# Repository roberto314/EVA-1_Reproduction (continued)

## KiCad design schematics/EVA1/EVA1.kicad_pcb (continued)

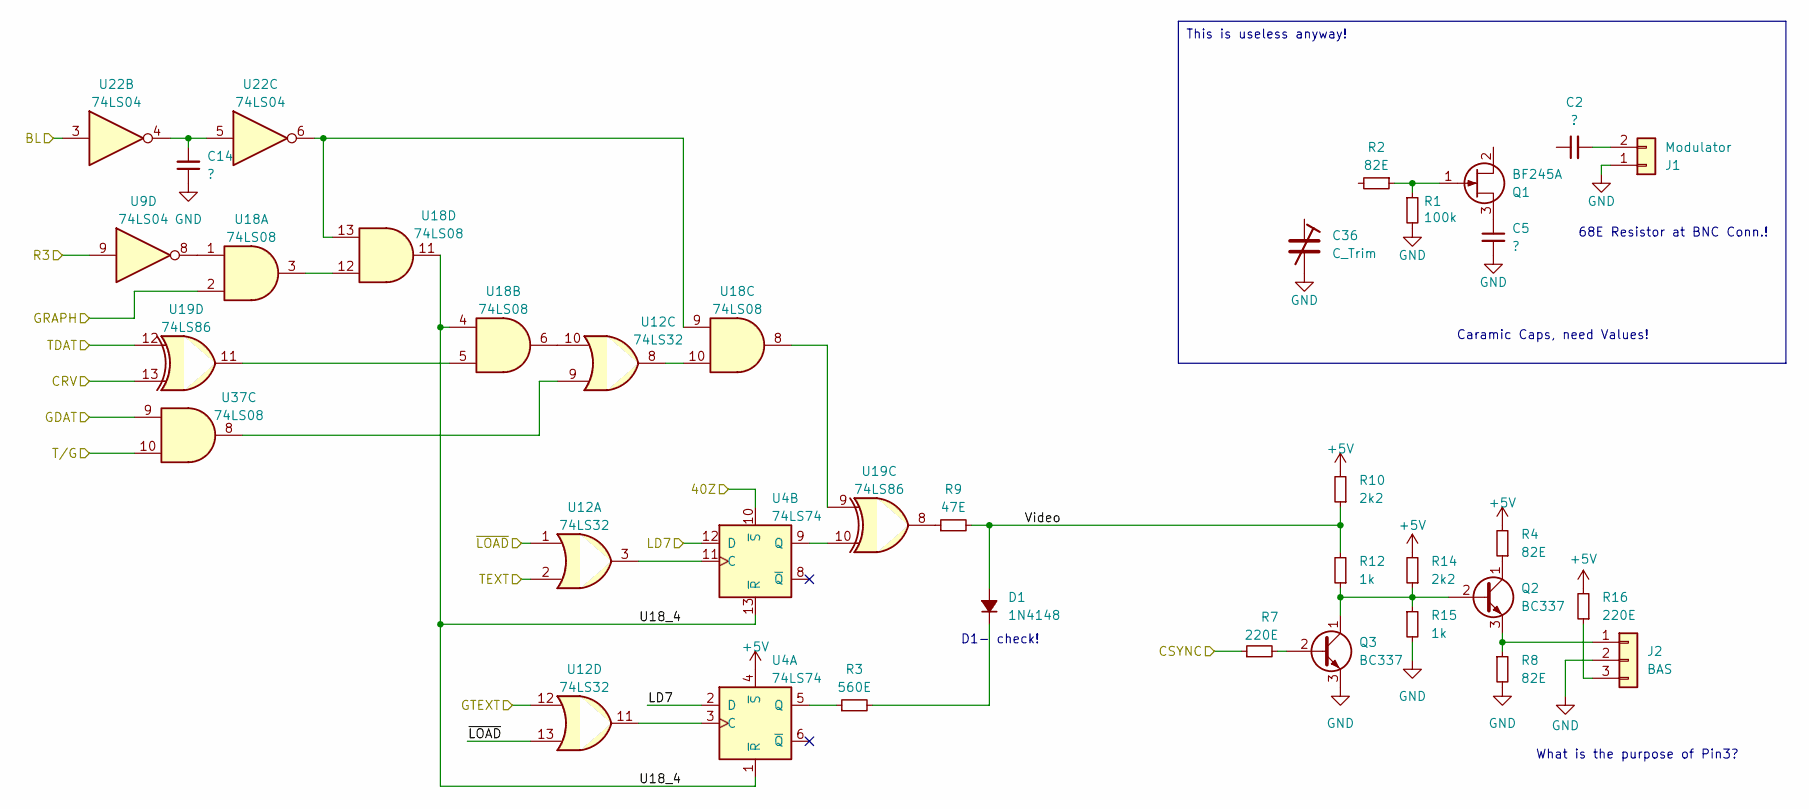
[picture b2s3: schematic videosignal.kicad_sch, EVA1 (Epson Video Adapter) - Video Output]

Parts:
C2, C5, C14: ?; C_Disc_D4.7mm_W2.5mm_P5.00mm
C36: C_Trim; C_Radial_D10.0mm_H20.0mm_P5.00mm
D1: 1N4148; D_A-405_P7.62mm_Horizontal
J1: Modulator; PinHeader_1x02_P2.54mm_Vertical
J2: BAS; PinHeader_1x03_P2.54mm_Vertical
Q1: BF245A; TO-92_Wide
Q2, Q3: BC337; TO-92_Wide
R1: 100k; R_Axial_DIN0411_L9.9mm_D3.6mm_P12.70mm_Horizontal
R2, R4, R8: 82E; R_Axial_DIN0411_L9.9mm_D3.6mm_P12.70mm_Horizontal
R3: 560E; R_Axial_DIN0411_L9.9mm_D3.6mm_P12.70mm_Horizontal
R7, R16: 220E; R_Axial_DIN0411_L9.9mm_D3.6mm_P12.70mm_Horizontal
R9: 47E; R_Axial_DIN0411_L9.9mm_D3.6mm_P12.70mm_Horizontal
R10, R14: 2k2; R_Axial_DIN0411_L9.9mm_D3.6mm_P12.70mm_Horizontal
R12, R15: 1k; R_Axial_DIN0411_L9.9mm_D3.6mm_P12.70mm_Horizontal
U4: 74LS74; DIP-14_W7.62mm
U9, U22: 74LS04; DIP-14_W7.62mm
U12: 74LS32; DIP-14_W7.62mm
U18, U37: 74LS08; DIP-14_W7.62mm
U19: 74LS86; DIP-14_W7.62mm

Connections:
+5V: R4.2, R10.2, R14.2, R16.2, U4.4 (~S); also elsewhere on the board
/BL: U22.3; also elsewhere on the board
/CRV: U19.13; also elsewhere on the board
/GDAT: U37.9; also elsewhere on the board
/GRAPH: U18.2; also elsewhere on the board
/GTEXT: U12.12; also elsewhere on the board
/LD7: U4.2 (D), U4.12 (D); also elsewhere on the board
/R3: U9.9; also elsewhere on the board
/TDAT: U19.12; also elsewhere on the board
/TEXT: U12.2; also elsewhere on the board
/T/G: U37.10; also elsewhere on the board
/Video Signal Genration/U18_4: U4.1 (~R), U4.13 (~R), U18.4, U18.11
/Video Signal Genration/Video: D1.2 (A), R9.2, R10.1, R12.2
/~40Z: U4.10 (~S); also elsewhere on the board
/~LOAD: U12.1, U12.13; also elsewhere on the board
GND: C5.2, C14.1, C36.2, J1.1, J2.2, Q3.3 (E), R1.2, R8.2, R15.2; also elsewhere on the board
unnamed: C14.2, U22.4, U22.5
unnamed: D1.1 (K), R3.2
unnamed: C2.2, J1.2
unnamed: J2.1, Q2.3 (E), R8.1
unnamed: J2.3, R16.1
unnamed: C5.1, Q1.3 (D)
unnamed: Q1.1 (G), R1.1, R2.1
unnamed: Q2.2 (B), Q3.1 (C), R12.1, R14.1, R15.1
unnamed: Q2.1 (C), R4.1
unnamed: Q3.2 (B), R7.2
unnamed 172: R7.1; also elsewhere on the board
unnamed: R9.1, U19.8
unnamed: U4.3 (C), U12.11
unnamed: R3.1, U4.5 (Q)
unnamed: U4.11 (C), U12.3
unnamed: U4.9 (Q), U19.10
unnamed: U12.8, U18.10
unnamed: U12.9, U37.8
unnamed: U12.10, U18.6
unnamed: U9.8, U18.1
unnamed: U18.5, U19.11
unnamed: U18.8, U19.9
unnamed: U18.3, U18.12
unnamed: U18.9, U18.13, U22.6

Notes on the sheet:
This is useless anyway!
D1- check!
Caramic Caps, need Values!
68E Resistor at BNC Conn.!
What is the purpose of Pin3?

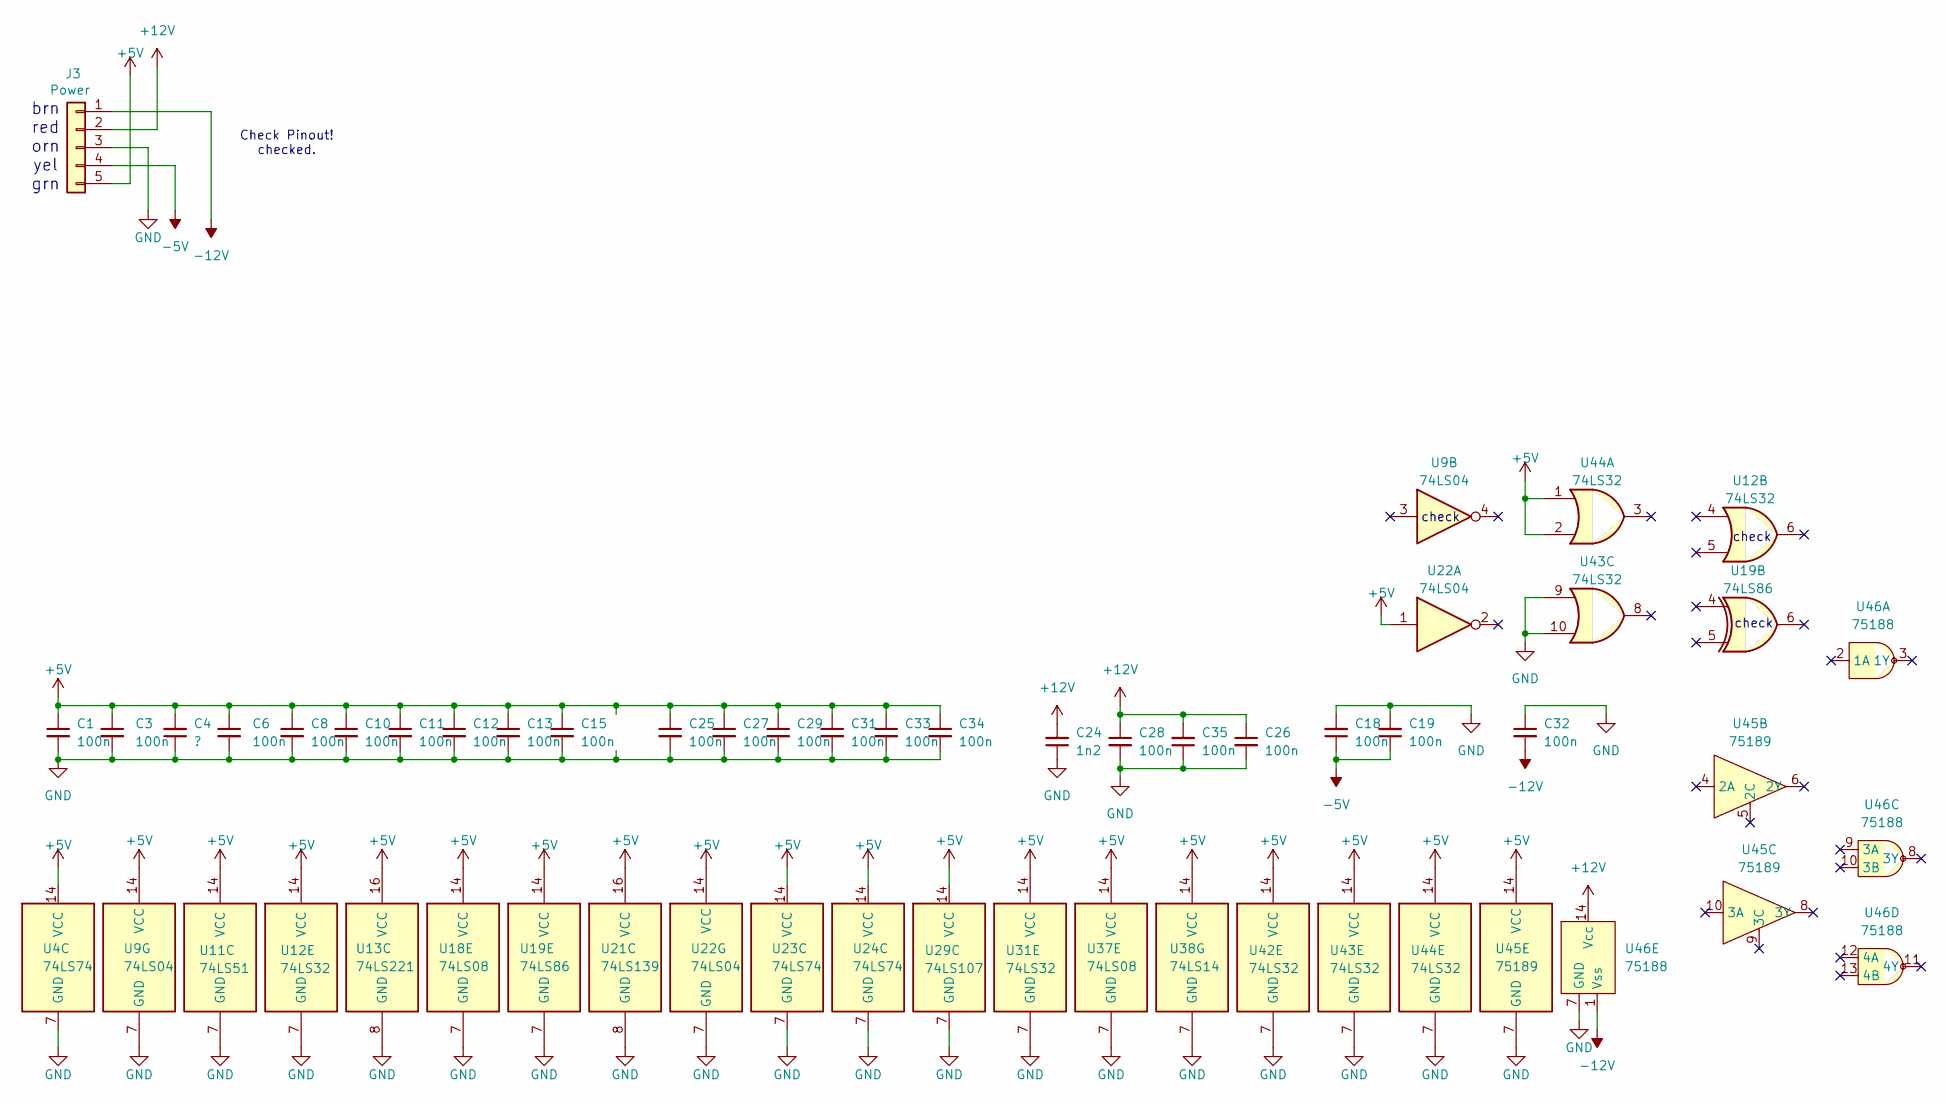
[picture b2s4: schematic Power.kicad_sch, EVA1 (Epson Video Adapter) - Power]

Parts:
C1, C3, C6, C8, C10, C11, C12, C13, C15, C18, C19, C25, C26, C27, C28, C29, C31, C32, C33, C34, C35: 100n; C_Disc_D4.7mm_W2.5mm_P5.00mm
C4: ?; C_Disc_D4.7mm_W2.5mm_P5.00mm
C24: 1n2; C_Disc_D4.7mm_W2.5mm_P5.00mm
J3: Power; PinHeader_1x05_P2.54mm_Vertical
U4, U23, U24: 74LS74; DIP-14_W7.62mm
U9, U22: 74LS04; DIP-14_W7.62mm
U11: 74LS51; DIP-14_W7.62mm
U12, U31, U42, U43, U44: 74LS32; DIP-14_W7.62mm
U13: 74LS221; DIP-16_W7.62mm
U18, U37: 74LS08; DIP-14_W7.62mm
U19: 74LS86; DIP-14_W7.62mm
U21: 74LS139; DIP-16_W7.62mm
U29: 74LS107; DIP-14_W7.62mm
U38: 74LS14; DIP-14_W7.62mm
U45: 75189; DIP-14_W7.62mm
U46: 75188; DIP-14_W7.62mm

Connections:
+5V: C1.1, C3.1, C4.2, C6.1, C8.1, C10.1, C11.1, C12.1, C13.1, C15.1, C25.1, C27.1, C29.1, C31.1, C33.1, C34.1, J3.5, U4.14 (VCC), U9.14 (VCC), U11.14 (VCC), U12.14 (VCC), U13.16 (VCC), U18.14 (VCC), U19.14 (VCC), U21.16 (VCC), U22.1, U22.14 (VCC), U23.14 (VCC), U24.14 (VCC), U29.14 (VCC), U31.14 (VCC), U37.14 (VCC), U38.14 (VCC), U42.14 (VCC), U43.14 (VCC), U44.1, U44.2, U44.14 (VCC), U45.14 (VCC); also elsewhere on the board
+12V: C24.2, C26.1, C28.1, C35.2, J3.2, U46.14 (Vcc); also elsewhere on the board
-5V: C18.1, C19.1, J3.4; also elsewhere on the board
-12V: C32.2, J3.1, U46.1 (Vss)
GND: C1.2, C3.2, C4.1, C6.2, C8.2, C10.2, C11.2, C12.2, C13.2, C15.2, C18.2, C19.2, C24.1, C25.2, C26.2, C27.2, C28.2, C29.2, C31.2, C32.1, C33.2, C34.2, C35.1, J3.3, U4.7 (GND), U9.7 (GND), U11.7 (GND), U12.7 (GND), U13.8 (GND), U18.7 (GND), U19.7 (GND), U21.8 (GND), U22.7 (GND), U23.7 (GND), U24.7 (GND), U29.7 (GND), U31.7 (GND), U37.7 (GND), U38.7 (GND), U42.7 (GND), U43.7 (GND), U43.9, U43.10, U44.7 (GND), U45.7 (GND), U46.7 (GND); also elsewhere on the board

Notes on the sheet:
Check Pinout! checked.
check
brn red orn yel grn

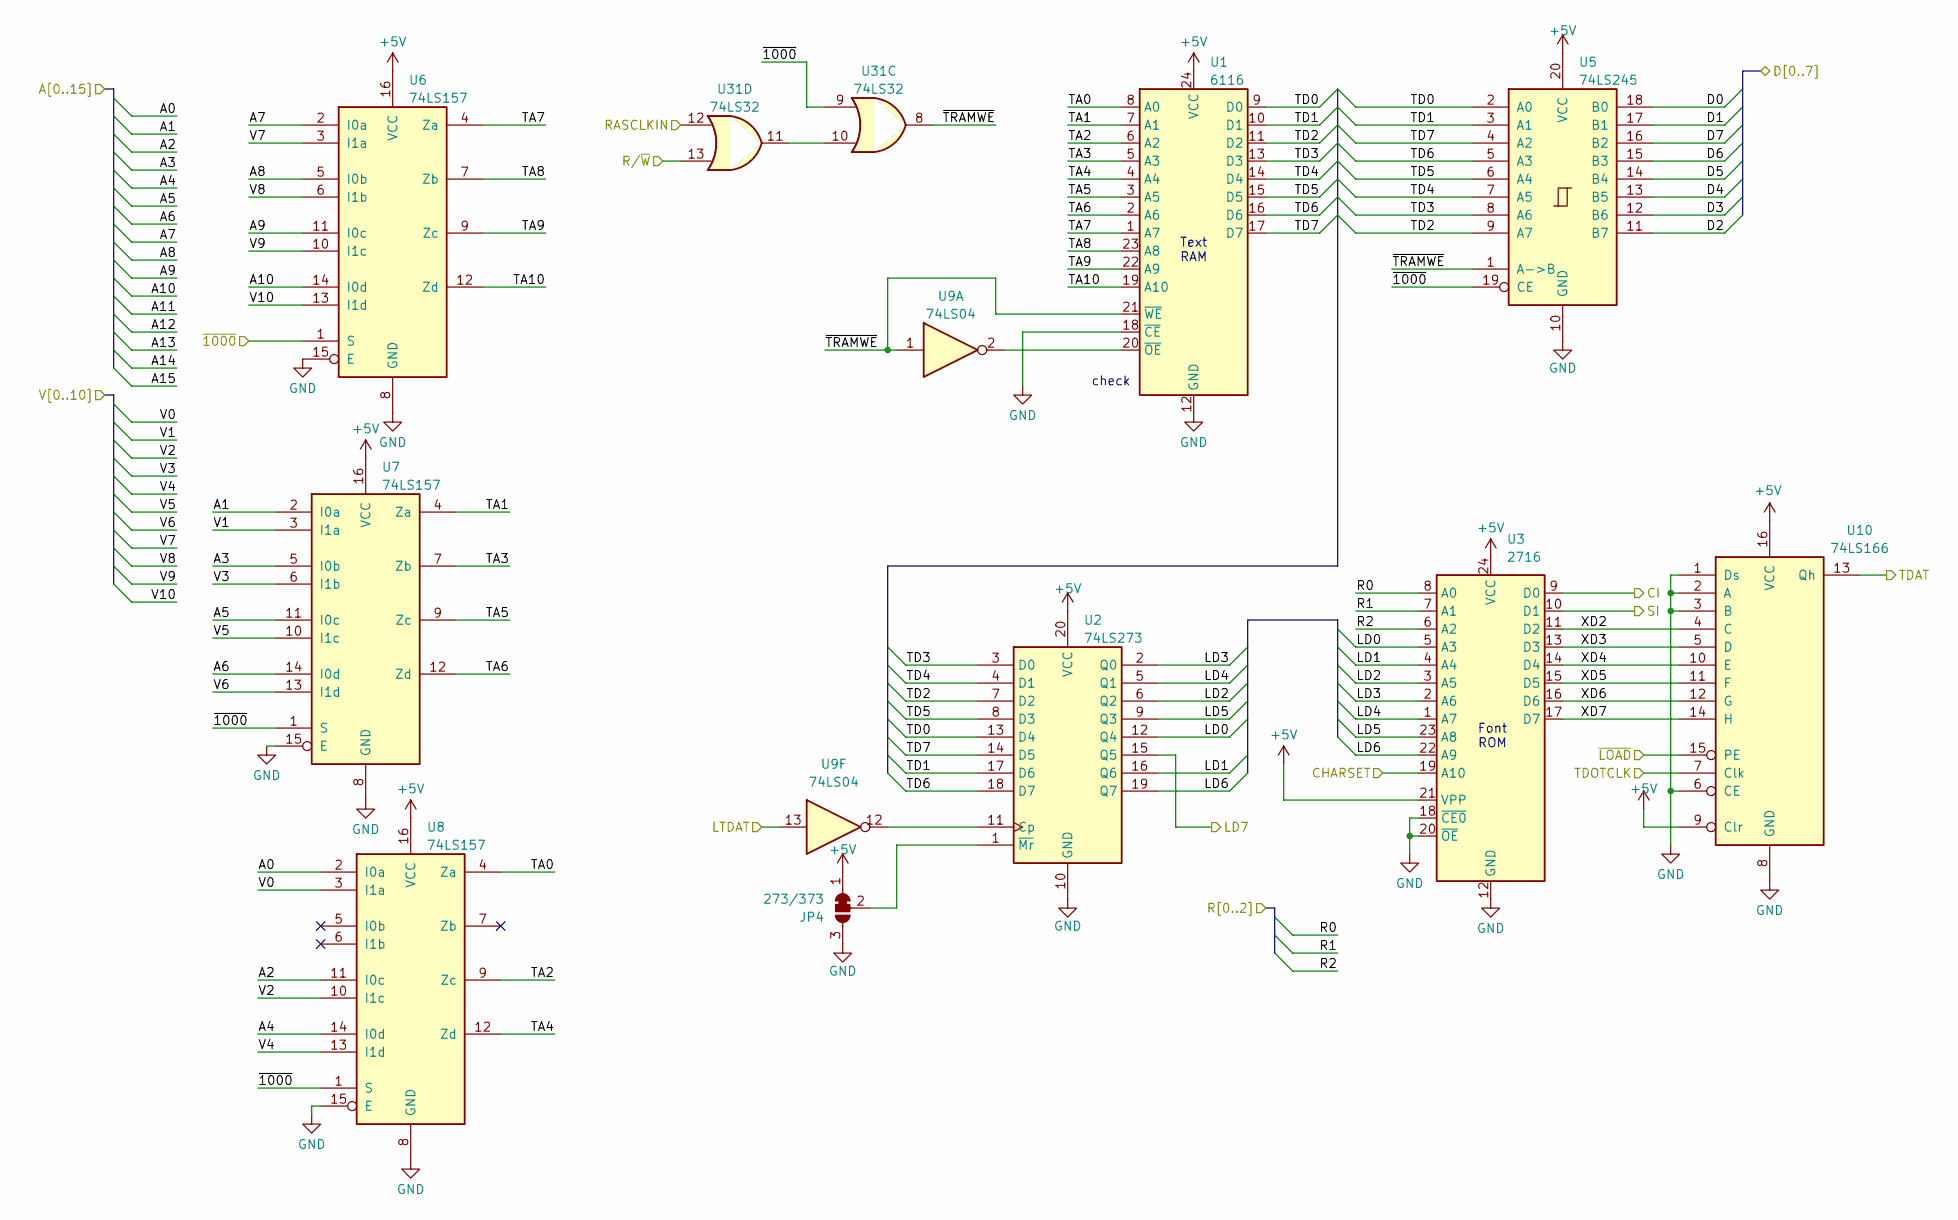
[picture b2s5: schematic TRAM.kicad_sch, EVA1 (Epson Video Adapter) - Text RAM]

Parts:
JP4: 273/373; SolderJumper-3_P1.3mm_Bridged12_RoundedPad1.0x1.5mm
U1: 6116; DIP-24_W15.24mm
U2: 74LS273; DIP-20_W7.62mm
U3: 2716; DIP-24_W15.24mm
U5: 74LS245; DIP-20_W7.62mm
U6, U7, U8: 74LS157; DIP-16_W7.62mm
U9: 74LS04; DIP-14_W7.62mm
U10: 74LS166; DIP-16_W7.62mm
U31: 74LS32; DIP-14_W7.62mm

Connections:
+5V: JP4.1 (A), U1.24 (VCC), U2.20 (VCC), U3.21 (VPP), U3.24 (VCC), U5.20 (VCC), U6.16 (VCC), U7.16 (VCC), U8.16 (VCC), U10.9 (Clr), U10.16 (VCC); also elsewhere on the board
/A0: U8.2 (I0a); also elsewhere on the board
/A1: U7.2 (I0a); also elsewhere on the board
/A2: U8.11 (I0c); also elsewhere on the board
/A3: U7.5 (I0b); also elsewhere on the board
/A4: U8.14 (I0d); also elsewhere on the board
/A5: U7.11 (I0c); also elsewhere on the board
/A6: U7.14 (I0d); also elsewhere on the board
/A7: U6.2 (I0a); also elsewhere on the board
/A8: U6.5 (I0b); also elsewhere on the board
/A9: U6.11 (I0c); also elsewhere on the board
/A10: U6.14 (I0d); also elsewhere on the board
/CHARSET: U3.19 (A10); also elsewhere on the board
/CI: U3.9 (D0)
/D0: U5.18 (B0); also elsewhere on the board
/D1: U5.17 (B1); also elsewhere on the board
/D2: U5.11 (B7); also elsewhere on the board
/D3: U5.12 (B6); also elsewhere on the board
/D4: U5.13 (B5); also elsewhere on the board
/D5: U5.14 (B4); also elsewhere on the board
/D6: U5.15 (B3); also elsewhere on the board
/D7: U5.16 (B2); also elsewhere on the board
/Graphic RAM, MUX and Shiftregister/RASCLKIN: U31.12; also elsewhere on the board
/LD7: U2.15 (Q5); also elsewhere on the board
/LTDAT: U9.13; also elsewhere on the board
/R0: U3.8 (A0); also elsewhere on the board
/R1: U3.7 (A1); also elsewhere on the board
/R2: U3.6 (A2); also elsewhere on the board
/R/~W: U31.13; also elsewhere on the board
/SI: U3.10 (D1)
/TDAT: U10.13 (Qh); also elsewhere on the board
/TDOTCLK: U10.7 (Clk); also elsewhere on the board
/Text RAM, MUX and Shiftregister1/LD0: U2.12 (Q4), U3.5 (A3)
/Text RAM, MUX and Shiftregister1/LD1: U2.16 (Q6), U3.4 (A4)
/Text RAM, MUX and Shiftregister1/LD2: U2.6 (Q2), U3.3 (A5)
/Text RAM, MUX and Shiftregister1/LD3: U2.2 (Q0), U3.2 (A6)
/Text RAM, MUX and Shiftregister1/LD4: U2.5 (Q1), U3.1 (A7)
/Text RAM, MUX and Shiftregister1/LD5: U2.9 (Q3), U3.23 (A8)
/Text RAM, MUX and Shiftregister1/LD6: U2.19 (Q7), U3.22 (A9)
/Text RAM, MUX and Shiftregister1/TA0: U1.8 (A0), U8.4 (Za)
/Text RAM, MUX and Shiftregister1/TA1: U1.7 (A1), U7.4 (Za)
/Text RAM, MUX and Shiftregister1/TA2: U1.6 (A2), U8.9 (Zc)
/Text RAM, MUX and Shiftregister1/TA3: U1.5 (A3), U7.7 (Zb)
/Text RAM, MUX and Shiftregister1/TA4: U1.4 (A4), U8.12 (Zd)
/Text RAM, MUX and Shiftregister1/TA5: U1.3 (A5), U7.9 (Zc)
/Text RAM, MUX and Shiftregister1/TA6: U1.2 (A6), U7.12 (Zd)
/Text RAM, MUX and Shiftregister1/TA7: U1.1 (A7), U6.4 (Za)
/Text RAM, MUX and Shiftregister1/TA8: U1.23 (A8), U6.7 (Zb)
/Text RAM, MUX and Shiftregister1/TA9: U1.22 (A9), U6.9 (Zc)
/Text RAM, MUX and Shiftregister1/TA10: U1.19 (A10), U6.12 (Zd)
/Text RAM, MUX and Shiftregister1/TD0: U1.9 (D0), U2.13 (D4), U5.2 (A0)
/Text RAM, MUX and Shiftregister1/TD1: U1.10 (D1), U2.17 (D6), U5.3 (A1)
/Text RAM, MUX and Shiftregister1/TD2: U1.11 (D2), U2.7 (D2), U5.9 (A7)
/Text RAM, MUX and Shiftregister1/TD3: U1.13 (D3), U2.3 (D0), U5.8 (A6)
/Text RAM, MUX and Shiftregister1/TD4: U1.14 (D4), U2.4 (D1), U5.7 (A5)
/Text RAM, MUX and Shiftregister1/TD5: U1.15 (D5), U2.8 (D3), U5.6 (A4)
/Text RAM, MUX and Shiftregister1/TD6: U1.16 (D6), U2.18 (D7), U5.5 (A3)
/Text RAM, MUX and Shiftregister1/TD7: U1.17 (D7), U2.14 (D5), U5.4 (A2)
/Text RAM, MUX and Shiftregister1/TRAMWE: U1.20 (~OE), U9.2
/Text RAM, MUX and Shiftregister1/XD2: U3.11 (D2), U10.4 (C)
/Text RAM, MUX and Shiftregister1/XD3: U3.13 (D3), U10.5 (D)
/Text RAM, MUX and Shiftregister1/XD4: U3.14 (D4), U10.10 (E)
/Text RAM, MUX and Shiftregister1/XD5: U3.15 (D5), U10.11 (F)
/Text RAM, MUX and Shiftregister1/XD6: U3.16 (D6), U10.12 (G)
/Text RAM, MUX and Shiftregister1/XD7: U3.17 (D7), U10.14 (H)
/Text RAM, MUX and Shiftregister1/~TRAMWE: U1.21 (~WE), U5.1 (A->B), U9.1, U31.8
/V0: U8.3 (I1a); also elsewhere on the board
/V1: U7.3 (I1a); also elsewhere on the board
/V2: U8.10 (I1c); also elsewhere on the board
/V3: U7.6 (I1b); also elsewhere on the board
/V4: U8.13 (I1d); also elsewhere on the board
/V5: U7.10 (I1c); also elsewhere on the board
/V6: U7.13 (I1d); also elsewhere on the board
/V7: U6.3 (I1a); also elsewhere on the board
/V8: U6.6 (I1b); also elsewhere on the board
/V9: U6.10 (I1c); also elsewhere on the board
/V10: U6.13 (I1d); also elsewhere on the board
/~1000: U5.19 (CE), U6.1 (S), U7.1 (S), U8.1 (S), U31.9; also elsewhere on the board
/~LOAD: U10.15 (PE); also elsewhere on the board
GND: JP4.3 (B), U1.12 (GND), U1.18 (~CE), U2.10 (GND), U3.12 (GND), U3.18 (~CE0), U3.20 (~OE), U5.10 (GND), U6.8 (GND), U6.15 (E), U7.8 (GND), U7.15 (E), U8.8 (GND), U8.15 (E), U10.1 (Ds), U10.2 (A), U10.3 (B), U10.6 (CE), U10.8 (GND); also elsewhere on the board
unnamed: JP4.2 (C), U2.1 (~Mr)
unnamed: U2.11 (Cp), U9.12
unnamed: U31.10, U31.11

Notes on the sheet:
Font ROM
check
Text RAM

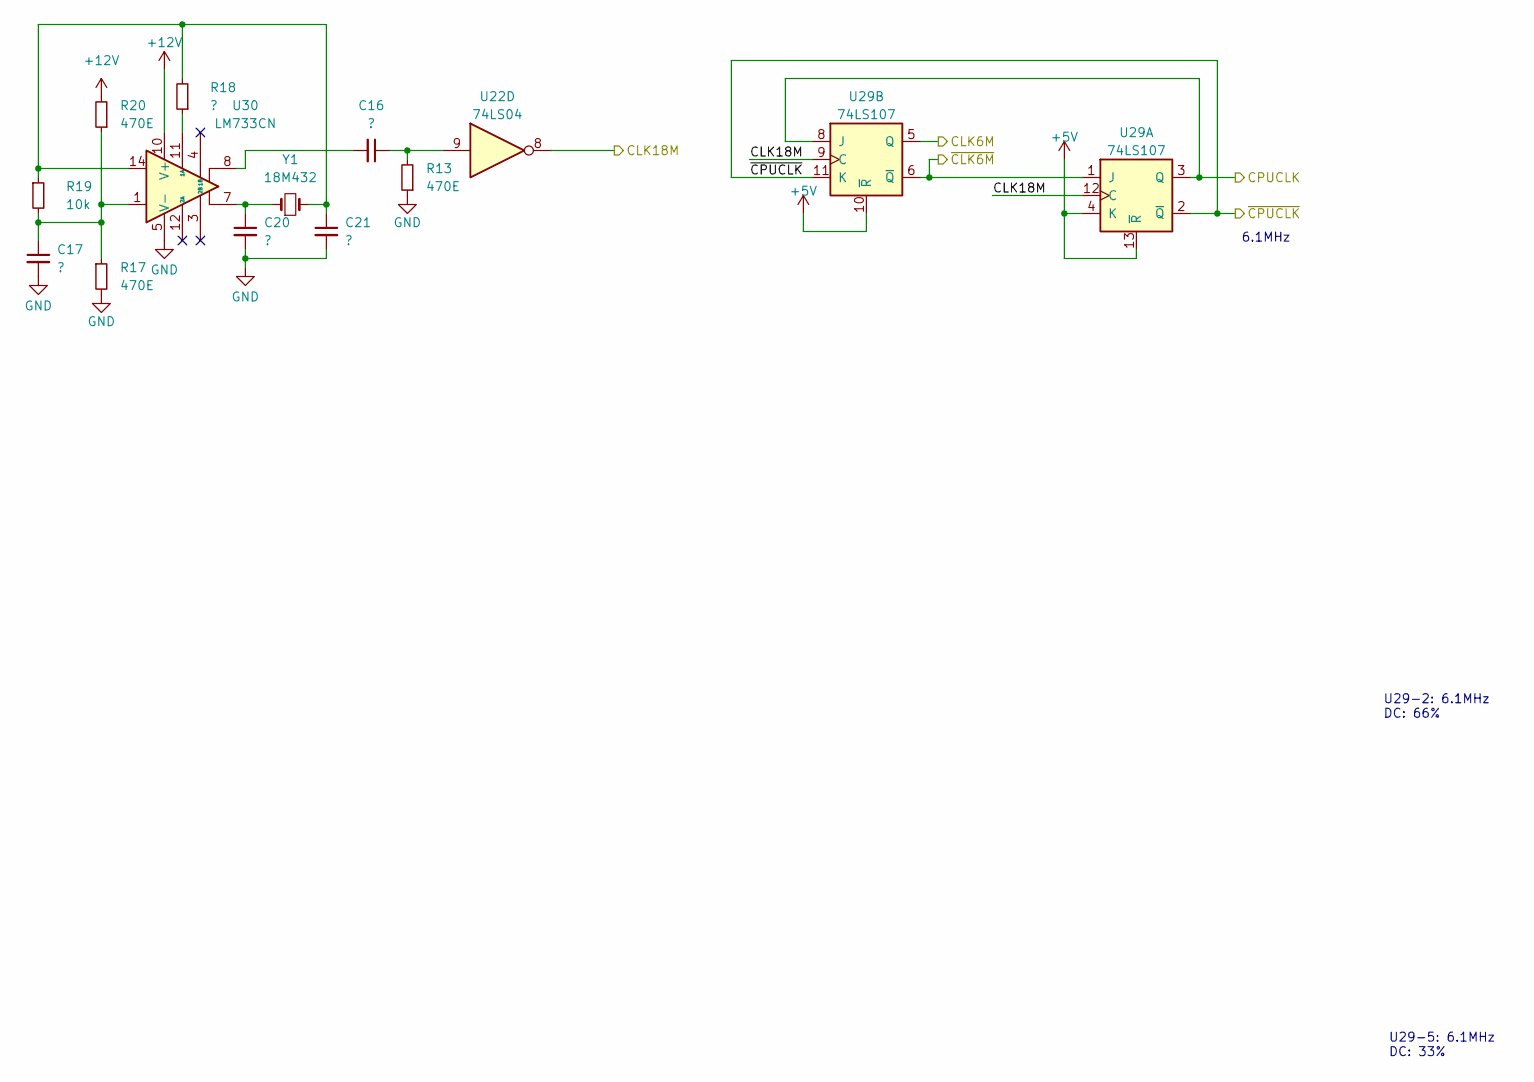
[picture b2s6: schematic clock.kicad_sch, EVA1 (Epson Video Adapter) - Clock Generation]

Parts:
C16, C17, C20, C21: ?; C_Disc_D4.7mm_W2.5mm_P5.00mm
R13, R17, R20: 470E; R_Axial_DIN0411_L9.9mm_D3.6mm_P12.70mm_Horizontal
R18: ?; R_Axial_DIN0204_L3.6mm_D1.6mm_P5.08mm_Horizontal
R19: 10k; R_Axial_DIN0204_L3.6mm_D1.6mm_P5.08mm_Horizontal
U22: 74LS04; DIP-14_W7.62mm
U29: 74LS107; DIP-14_W7.62mm
U30: LM733CN; DIP-14_W7.62mm
Y1: 18M432; Crystal_HC49-U_Vertical

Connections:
+5V: U29.4 (K), U29.10 (~R), U29.13 (~R); also elsewhere on the board
+12V: R20.2, U30.10 (V+); also elsewhere on the board
/CLK6M: U29.5 (Q); also elsewhere on the board
/CLK18M: U22.8, U29.9 (C), U29.12 (C); also elsewhere on the board
/CPUCLK: U29.3 (Q), U29.8 (J); also elsewhere on the board
/~CLK6M: U29.1 (J), U29.6 (~Q); also elsewhere on the board
/~CPUCLK: U29.2 (~Q), U29.11 (K); also elsewhere on the board
GND: C17.2, C20.2, C21.2, R13.1, R17.2, U30.5 (V-); also elsewhere on the board
unnamed: C16.1, R13.2, U22.9
unnamed: C16.2, U30.8
unnamed: C17.1, R17.1, R19.2, R20.1, U30.1
unnamed: C20.1, U30.7, Y1.1
unnamed: C21.1, R18.2, R19.1, U30.14, Y1.2
unnamed: R18.1, U30.11 (1A)

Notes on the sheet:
U29-2: 6.1MHz DC: 66%
6.1MHz
U29-5: 6.1MHz DC: 33%

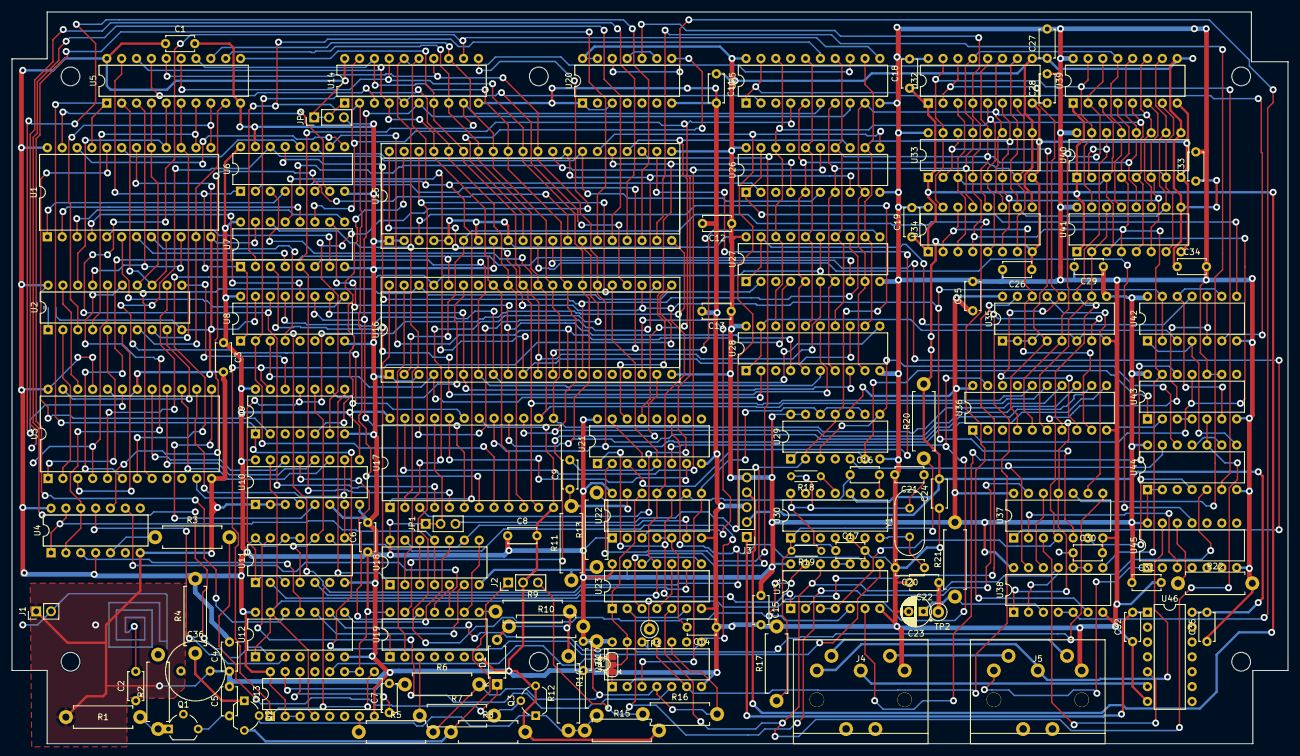
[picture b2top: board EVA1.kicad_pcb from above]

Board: 2 copper layers, 218.0 x 125.0 mm, 126 parts (1 on the bottom side), 207 nets.

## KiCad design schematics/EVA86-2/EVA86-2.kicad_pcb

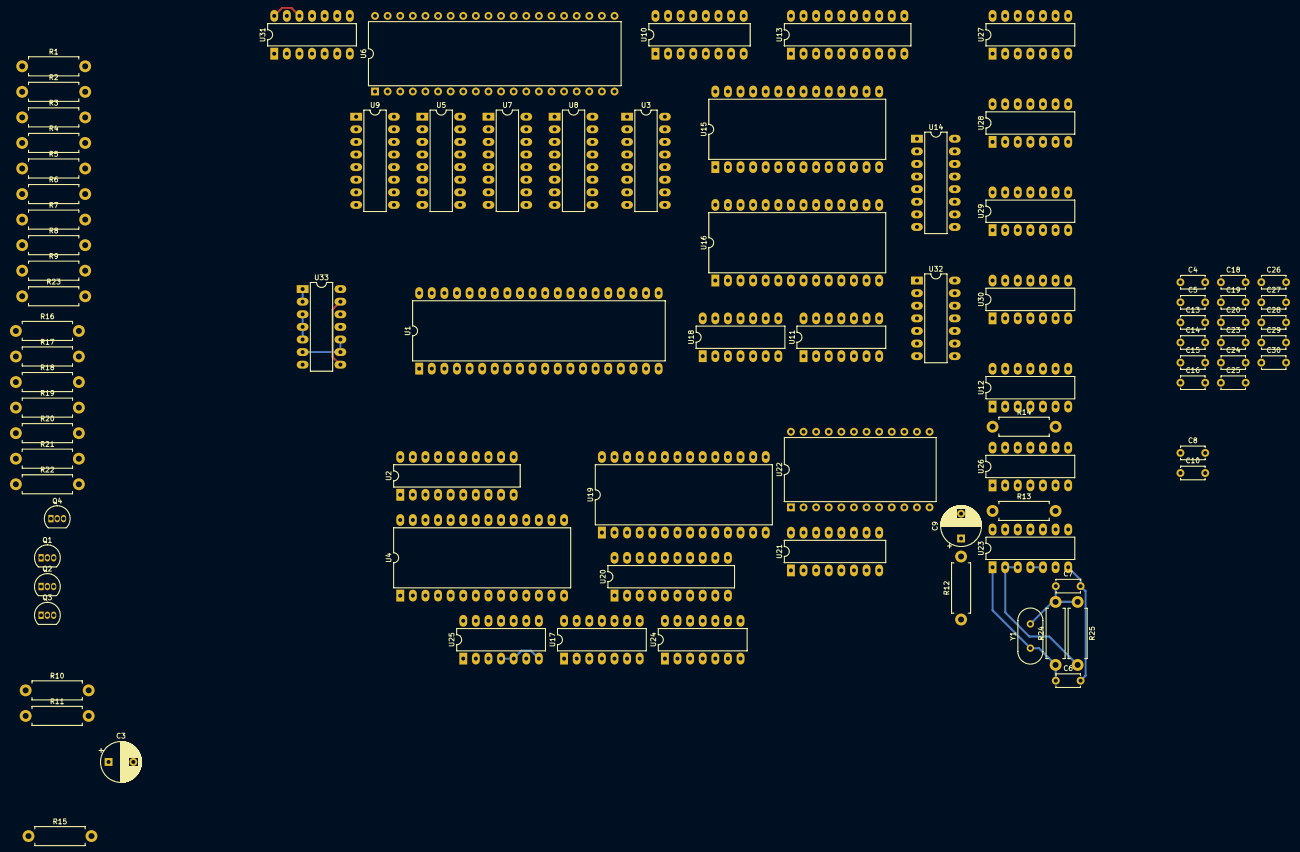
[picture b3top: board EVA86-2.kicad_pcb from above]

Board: 2 copper layers, 86 parts (0 on the bottom side), 172 nets.

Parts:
C3: 47u/25; CP_Radial_D8.0mm_P5.00mm
C4, C5, C8, C13, C14, C15, C16, C18, C19, C20, C27: 100n; C_Disc_D4.7mm_W2.5mm_P5.00mm
C6: 22p; C_Disc_D4.7mm_W2.5mm_P5.00mm
C7: 47p; C_Disc_D4.7mm_W2.5mm_P5.00mm
C9: 47u; CP_Radial_D8.0mm_P5.00mm
C10: 220p; C_Disc_D4.7mm_W2.5mm_P5.00mm
C23, C24, C25, C26, C28, C29, C30: 22n; C_Disc_D4.7mm_W2.5mm_P5.00mm
Q1, Q2, Q3, Q4: BC337; TO-92_Inline
R1, R14: 2k2; R_Axial_DIN0411_L9.9mm_D3.6mm_P12.70mm_Horizontal
R2, R4, R6, R7, R8, R9, R17, R21: 1k; R_Axial_DIN0411_L9.9mm_D3.6mm_P12.70mm_Horizontal
R3, R12, R23: 10k; R_Axial_DIN0411_L9.9mm_D3.6mm_P12.70mm_Horizontal
R5: 4k7; R_Axial_DIN0411_L9.9mm_D3.6mm_P12.70mm_Horizontal
R10: 100E; R_Axial_DIN0411_L9.9mm_D3.6mm_P12.70mm_Horizontal
R11, R18, R22: 220E; R_Axial_DIN0411_L9.9mm_D3.6mm_P12.70mm_Horizontal
R13, R24: 100k; R_Axial_DIN0411_L9.9mm_D3.6mm_P12.70mm_Horizontal
R15, R25: 1k2; R_Axial_DIN0411_L9.9mm_D3.6mm_P12.70mm_Horizontal
R16: 390E; R_Axial_DIN0411_L9.9mm_D3.6mm_P12.70mm_Horizontal
R19: 82E; R_Axial_DIN0411_L9.9mm_D3.6mm_P12.70mm_Horizontal
R20: 10E; R_Axial_DIN0411_L9.9mm_D3.6mm_P12.70mm_Horizontal
U1: MC6803; DIP-40_W15.24mm_LongPads
U2: 74LS373; DIP-20_W7.62mm_LongPads
U3: 74LS139; DIP-16_W7.62mm_LongPads
U4: 27C64; DIP-28_W15.24mm_LongPads
U5, U7, U8, U9, U10: 74LS257; DIP-16_W7.62mm_LongPads
U6: MC6845; DIP-40_W15.24mm
U11, U31: 74LS86; DIP-14_W7.62mm_LongPads
U12, U25, U30: 74LS00; DIP-14_W7.62mm_LongPads
U13, U20: 74LS245; DIP-20_W7.62mm_LongPads
U14, U21: 74LS165; DIP-16_W7.62mm_LongPads
U15, U16, U19: UM6264DM; DIP-28_W15.24mm_LongPads
U17, U24: 74LS74; DIP-14_W7.62mm_LongPads
U18, U33: 74LS32; DIP-14_W7.62mm_LongPads
U22: 27C32; DIP-24_W15.24mm
U23: 74HC04; DIP-14_W7.62mm_LongPads
U26, U27: 74LS293; DIP-14_W7.62mm_LongPads
U28, U29: 74LS107; DIP-14_W7.62mm_LongPads
U32: 74LS08; DIP-14_W7.62mm_LongPads
Y1: 19M66; Crystal_HC49-U_Vertical

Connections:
+5V: C4.2, C13.1, C14.1, C15.1, C16.1, C18.1, C19.1, C20.1, C23.1, C24.1, C25.1, C26.1, C27.1, C28.1, C29.1, C30.1, Q4.1 (C), R5.1, R12.1, R17.1, R21.1, R23.1, U1.4 (~NMI), U1.7 (VCC), U1.21 (VCC_STBY), U2.20 (VCC), U3.16 (VCC), U4.1 (VPP), U4.27 (~PGM), U4.28 (VCC), U5.16 (VCC), U6.20 (VCC), U7.16 (VCC), U8.16 (VCC), U9.16 (VCC), U10.16 (VCC), U11.9, U11.13, U11.14 (VCC), U12.12, U12.14 (VCC), U13.20 (VCC), U14.16 (VCC), U15.26 (CS2), U15.28 (VDD), U16.26 (CS2), U16.28 (VDD), U17.1 (~R), U17.4 (~S), U17.10 (~S), U17.13 (~R), U17.14 (VCC), U18.14 (VCC), U19.26 (CS2), U19.28 (VDD), U20.20 (VCC), U21.16 (VCC), U22.24 (VCC), U23.14 (VCC), U24.1 (~R), U24.11 (C), U24.12 (D), U24.14 (VCC), U25.12, U25.14 (VCC), U26.14 (VCC), U27.13 (Mr2), U27.14 (VCC), U28.1 (J), U28.4 (K), U28.13 (~R), U28.14 (VCC), U29.4 (K), U29.13 (~R), U29.14 (VCC), U30.14 (VCC), U31.5, U31.12, U31.14 (VCC), U32.14 (VCC), U33.14 (VCC)
+12V: C3.2, R2.1, R7.1, R10.2
/A0: U2.6 (O2), U4.10 (A0), U5.2 (I0a), U6.24 (RS)
/A1: U2.16 (O6), U4.9 (A1), U5.5 (I0b)
/A2: U2.19 (O7), U4.8 (A2), U5.11 (I0d)
/A3: U2.2 (O0), U4.7 (A3), U5.14 (I0c)
/A4: U2.5 (O1), U4.6 (A4), U7.2 (I0a)
/A5: U2.9 (O3), U4.5 (A5), U7.5 (I0b)
/A6: U2.12 (O4), U4.4 (A6), U7.11 (I0d), U9.5 (I0b)
/A7: U2.15 (O5), U4.3 (A7), U7.14 (I0c), U9.2 (I0a)
/A8: U1.29 (P40/A8), U4.25 (A8), U8.5 (I0b), U9.11 (I0d)
/A9: U1.28 (P41/A9), U4.24 (A9), U8.2 (I0a), U9.14 (I0c)
/A10: U1.27 (P42/A10), U4.21 (A10), U8.14 (I0c), U10.2 (I0a)
/A11: U1.26 (P43/A11), U4.23 (A11), U8.11 (I0d), U10.5 (I0b)
/A12: U1.25 (P44/A12), U3.2 (A0), U4.2 (A12), U10.11 (I0d)
/A13: U1.24 (P45/A13), U3.3 (A1), U10.14 (I0c)
/A14: U1.23 (P46/A14), U3.14 (A0)
/A15: U1.22 (P47/A15), U3.13 (A1)
/CPUCLK: U1.3 (EXTAL), U12.8
/Clock/GRAPH: R14.1, U12.13, U28.10 (~R)
/Clock/~GRAPH: U12.11, U29.10 (~R)
/D0: U1.37 (P30/AD0), U2.7 (D2), U4.11 (D0), U6.33 (D0), U13.16 (B2), U20.17 (B1)
/D1: U1.36 (P31/AD1), U2.17 (D6), U4.12 (D1), U6.32 (D1), U13.14 (B4), U20.15 (B3)
/D2: U1.35 (P32/AD2), U2.18 (D7), U4.13 (D2), U6.31 (D2), U13.12 (B6), U20.12 (B6)
/D3: U1.34 (P33/AD3), U2.3 (D0), U4.15 (D3), U6.30 (D3), U13.11 (B7), U20.14 (B4)
/D4: U1.33 (P34/AD4), U2.4 (D1), U4.16 (D4), U6.29 (D4), U13.13 (B5), U20.13 (B5)
/D5: U1.32 (P35/AD5), U2.8 (D3), U4.17 (D5), U6.28 (D5), U13.15 (B3), U20.11 (B7)
/D6: U1.31 (P36/AD6), U2.13 (D4), U4.18 (D6), U6.27 (D6), U13.17 (B1), U20.16 (B2)
/D7: U1.30 (P37/AD7), U2.14 (D5), U4.19 (D7), U6.26 (D7), U13.18 (B0), U20.18 (B0)
/DOTCLK: U14.2 (CP), U21.2 (CP), U28.2 (~Q)
/DOUT: R3.1, R8.2
/DOUT#: Q3.1 (C), R7.2
/E: R15.1, U1.40 (E), U3.15 (E), U6.23 (E), U31.2
/GA0: U5.4 (Za), U15.10 (A0), U16.10 (A0), U19.10 (A0)
/GA1: U5.7 (Zb), U15.9 (A1), U16.9 (A1), U19.9 (A1)
/GA2: U5.9 (Zd), U15.8 (A2), U16.8 (A2), U19.8 (A2)
/GA3: U5.12 (Zc), U15.7 (A3), U16.7 (A3), U19.7 (A3)
/GA4: U7.4 (Za), U15.6 (A4), U16.6 (A4), U19.6 (A4)
/GA5: U7.7 (Zb), U15.5 (A5), U16.5 (A5), U19.5 (A5)
/GA6: U9.7 (Zb), U15.4 (A6), U16.4 (A6)
/GA7: U9.4 (Za), U15.3 (A7), U16.3 (A7)
/GA8: U9.9 (Zd), U15.25 (A8), U16.25 (A8)
/GA9: U9.12 (Zc), U15.24 (A9), U16.24 (A9)
/GA10: U10.4 (Za), U15.21 (A10), U16.21 (A10)
/GA11: U10.7 (Zb), U15.23 (A11), U16.23 (A11)
/GA12: U10.9 (Zd), U15.2 (A12), U16.2 (A12)
/GA13: U10.12 (Zc), U11.12, U15.20 (~CS1)
/GRAPH: U1.14 (P11/TOUT2), U12.1
/GTEXT: U1.15 (P12/TOUT3), U19.2 (A12)
/Graphics/BL: U6.18 (DE), U17.12 (D)
/Graphics/CI: U18.4, U22.9 (D0)
/Graphics/CRV: U6.19 (CURSOR), U17.2 (D)
/Graphics/GD0: U13.4 (A2), U14.11 (D0), U15.11 (DQ0), U16.11 (DQ0)
/Graphics/GD1: U13.6 (A4), U14.12 (D1), U15.12 (DQ1), U16.12 (DQ1)
/Graphics/GD2: U13.8 (A6), U14.13 (D2), U15.13 (DQ2), U16.13 (DQ2)
/Graphics/GD3: U13.9 (A7), U14.14 (D3), U15.15 (DQ3), U16.15 (DQ3)
/Graphics/GD4: U13.7 (A5), U14.3 (D4), U15.16 (DQ4), U16.16 (DQ4)
/Graphics/GD5: U13.5 (A3), U14.4 (D5), U15.17 (DQ5), U16.17 (DQ5)
/Graphics/GD6: U13.3 (A1), U14.5 (D6), U15.18 (DQ6), U16.18 (DQ6)
/Graphics/GD7: U13.2 (A0), U14.6 (D7), U15.19 (DQ7), U16.19 (DQ7)
/Graphics/GDAT: U12.2, U14.9 (Q7)
/Graphics/PX0: U21.13 (D2), U22.11 (D2)
/Graphics/PX1: U21.14 (D3), U22.13 (D3)
/Graphics/PX2: U21.3 (D4), U22.14 (D4)
/Graphics/PX3: U21.4 (D5), U22.15 (D5)
/Graphics/PX4: U21.5 (D6), U22.16 (D6)
/Graphics/PX5: U21.6 (D7), U22.17 (D7)
/Graphics/R3: U6.35 (RA3), U25.13
/Graphics/SI: U22.10 (D1), U24.2 (D)
/Graphics/TD0: U19.11 (DQ0), U20.3 (A1), U22.5 (A3)
/Graphics/TD1: U19.12 (DQ1), U20.5 (A3), U22.4 (A4)
/Graphics/TD2: U19.13 (DQ2), U20.8 (A6), U22.3 (A5)
/Graphics/TD3: U19.15 (DQ3), U20.6 (A4), U22.2 (A6)
/Graphics/TD4: U19.16 (DQ4), U20.7 (A5), U22.1 (A7)
/Graphics/TD5: U19.17 (DQ5), U20.9 (A7), U22.23 (A8)
/Graphics/TD6: U19.18 (DQ6), U20.4 (A2), U22.22 (A9)
/Graphics/TD7: U19.19 (DQ7), U20.2 (A0), U22.19 (A10)
/Graphics/TDAT: U11.5, U21.9 (Q7)
/Graphics/~GWR: U13.1 (A->B), U15.27 (~WE), U16.27 (~WE), U18.11
/Graphics/~TWR: U18.3, U19.27 (~WE), U20.1 (A->B)
/OPT: U1.20 (P17), U22.21 (A11)
/RX: Q2.1 (C), R5.2, U1.11 (P23/RX)
/R/~W: U1.38 (SC2/R/~W), U6.22 (R/~W), U33.12
/TA6: U7.9 (Zd), U19.4 (A6)
/TA7: U7.12 (Zc), U19.3 (A7)
/TA8: U8.7 (Zb), U19.25 (A8)
/TA9: U8.4 (Za), U19.24 (A9)
/TA10: U8.12 (Zc), U19.21 (A10)
/TA11: U8.9 (Zd), U19.23 (A11)
/TEXT: U1.16 (P13), U12.4
/TX: R6.2, U1.12 (P24/TX)
/Video/R0: U6.38 (RA0), U9.6 (I1b)
/Video/R1: U6.37 (RA1), U9.3 (I1a)
/Video/R2: U6.36 (RA2), U9.10 (I1d)
/Video/V0: U5.3 (I1a), U6.4 (MA0)
/Video/V1: U5.6 (I1b), U6.5 (MA1)
/Video/V2: U5.10 (I1d), U6.6 (MA2)
/Video/V3: U5.13 (I1c), U6.7 (MA3)
/Video/V4: U6.8 (MA4), U7.3 (I1a)
/Video/V5: U6.9 (MA5), U7.6 (I1b)
/Video/V6: U6.10 (MA6), U7.10 (I1d), U9.13 (I1c)
/Video/V7: U6.11 (MA7), U7.13 (I1c), U10.3 (I1a)
/Video/V8: U6.12 (MA8), U8.6 (I1b), U10.6 (I1b)
/Video/V9: U6.13 (MA9), U8.3 (I1a), U10.10 (I1d)
/Video/V10: U6.14 (MA10), U8.13 (I1c), U10.13 (I1c)
/Video/V/~C: U5.1 (S), U7.1 (S), U8.1 (S), U9.1 (S), U10.1 (S), U32.3
/~40Z: R1.1, U1.13 (P10/TIN2), U23.13, U30.9
/~CEROM: U3.9 (O3), U4.22 (~OE)
/~CRT: U3.6 (O2), U6.25 (~CS)
/~E: U6.21 (CLK), U31.11, U33.1, U33.2
/~GRAM: U3.10 (O2), U13.19 (CE), U18.13, U32.1
/~IRQ: R23.2, U1.5 (~IRQ1)
/~LD: U14.1 (~PL), U17.3 (C), U17.11 (C), U18.5, U18.10, U21.1 (~PL), U24.3 (C), U31.6
/~RST: U1.6 (~RST), U6.2 (~RESET), U23.8
/~TRAM: U3.11 (O1), U18.2, U20.19 (CE), U32.2
/~WR: U18.1, U18.12, U33.11
GND: C3.1, C4.1, C5.1, C6.2, C7.2, C8.2, C9.2, C10.2, C13.2, C14.2, C15.2, C16.2, C18.2, C19.2, C20.2, C23.2, C24.2, C25.2, C26.2, C27.2, C28.2, C29.2, C30.2, Q1.3 (E), Q2.3 (E), Q3.3 (E), R1.2, R3.2, R9.2, R13.2, R14.2, R16.2, R19.2, U1.1 (GND), U1.2 (XTAL), U1.9 (P21/TOUT1), U2.1 (OE), U2.10 (GND), U3.8 (GND), U4.14 (GND), U4.20 (~CE), U5.8 (GND), U5.15 (OE), U6.1 (GND), U6.3 (LPSTB), U7.8 (GND), U7.15 (OE), U8.8 (GND), U8.10 (I1d), U8.15 (OE), U9.8 (GND), U9.15 (OE), U10.8 (GND), U10.15 (OE), U11.7 (GND), U12.7 (GND), U13.10 (GND), U14.8 (GND), U14.10 (DS), U14.15 (~CE), U15.14 (VSS), U15.22 (~OE), U16.14 (VSS), U16.22 (~OE), U17.7 (GND), U18.7 (GND), U19.14 (VSS), U19.20 (~CS1), U19.22 (~OE), U20.10 (GND), U21.8 (GND), U21.10 (DS), U21.11 (D0), U21.12 (D1), U21.15 (~CE), U22.12 (GND), U22.18 (~CE), U22.20 (~OE/VPP), U23.7 (GND), U24.7 (GND), U25.4, U25.5, U25.7 (GND), U26.7 (GND), U26.12 (Mr1), U26.13 (Mr2), U27.7 (GND), U28.7 (GND), U29.7 (GND), U30.7 (GND), U31.7 (GND), U32.7 (GND), U33.7 (GND)
unnamed: C6.1, R24.1, U23.1, Y1.1
unnamed: C7.1, R24.2, R25.1, Y1.2
unnamed: C9.1, R12.2, R13.1, U23.11
unnamed: C5.2, R10.1, R11.1
unnamed: Q1.1 (C), R2.2
unnamed: Q2.2 (B), R4.2
unnamed: C10.1, R15.2, U31.1, U31.13
unnamed: R16.1, R17.2, R18.1
unnamed: R21.2, R22.2
unnamed: U1.39 (SC1/AS), U25.9, U25.10
unnamed: Q1.2 (B), R6.1
unnamed: Q3.2 (B), R8.1, R9.1
unnamed: Q4.2 (B), R18.2
unnamed: Q4.3 (E), R19.1, R20.1
unnamed: R22.1, U32.6
unnamed: R25.2, U23.2, U23.3
unnamed: U3.1 (E), U3.12 (O0)
unnamed: U6.39 (HS), U31.10
unnamed: U6.40 (VS), U31.9
unnamed: U11.2, U30.11
unnamed: U11.3, U32.5
unnamed: U11.6, U32.9
unnamed: U12.3, U30.13
unnamed: U12.5, U32.8
unnamed: U12.6, U30.12
unnamed: U11.11, U16.20 (~CS1)
unnamed: U11.4, U17.5 (Q)
unnamed: U17.9 (Q), U32.4, U32.13
unnamed: U23.4, U23.5
unnamed: U23.12, U30.1
unnamed: U18.9, U24.5 (Q)
unnamed: U24.4 (~S), U32.11
unnamed: U11.1, U24.9 (Q)
unnamed: U18.6, U24.13 (~R)
unnamed: U18.8, U24.10 (~S)
unnamed: U25.1, U25.2, U31.8
unnamed: U25.11, U32.10, U32.12
unnamed: U23.6, U26.10 (Cp0), U30.10
unnamed: U26.9 (Q0), U26.11 (Cp1), U30.2
unnamed: U26.5 (Q1), U27.11 (Cp1)
unnamed: U27.8 (Q3), U27.10 (Cp0)
unnamed: C8.1, U23.9, U23.10, U27.12 (Mr1)
unnamed: U11.10, U27.9 (Q0)
unnamed: U28.9 (C), U28.12 (C), U29.9 (C), U29.12 (C), U30.6
unnamed: U28.3 (Q), U28.8 (J), U28.11 (K)
unnamed: U12.10, U28.6 (~Q)
unnamed: U12.9, U29.1 (J), U29.6 (~Q)
unnamed: U29.3 (Q), U29.8 (J)
unnamed: U29.2 (~Q), U29.11 (K)
unnamed: U30.3, U30.4
unnamed: U30.5, U30.8
unnamed: U31.3, U31.4
unnamed: U33.3, U33.4, U33.5
unnamed: U33.6, U33.9, U33.10
unnamed: U33.8, U33.13

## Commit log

2025-04-19 new upload
2025-04-24 monitor added
2025-04-24 datasheets added
2025-05-10 disassembly commented
2025-05-11 new functions in assembly
2025-05-12 new schematic added, documentation added
2025-06-01 assemble script updated, documentation is now as pdf avail.
2025-06-02 schematics updated
2025-06-02 schematics backup cleaned
2025-11-07 New version for production
2025-11-07 BOM added
2025-11-07 Readme modified
2025-11-07 BOM updated
2025-12-04 BOM updated, GAL eq. updated
2025-12-04 Schematic and Board updated
2025-12-04 Readme updated
2025-12-06 pics added, Readme udated
2025-12-06 Readme udated
2025-12-15 new Gerber files
2025-12-19 User Manual udated
2025-12-19 firmware for arduino and rp2040 added
